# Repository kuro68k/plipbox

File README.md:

# plipbox

PCB for lallafa's plipbox (http://lallafa.de/blog/amiga-projects/plipbox/).

Allows an Amiga to connect to an ethernet network via the parallel port. Very low cost, uses an Arduino Nano V3 and ethernet shield.

This PCB is 2 layers. There is no cost advantage to single layer when ordering from Chinese manufacturers like Seeed Studio, and two layers means no need for jumper wires.

In addition there is a low cost TTL to RS232 level shifter. It's entirely optional, and if fitted allows the Amiga to configure the plipbox via connection to the serial port.

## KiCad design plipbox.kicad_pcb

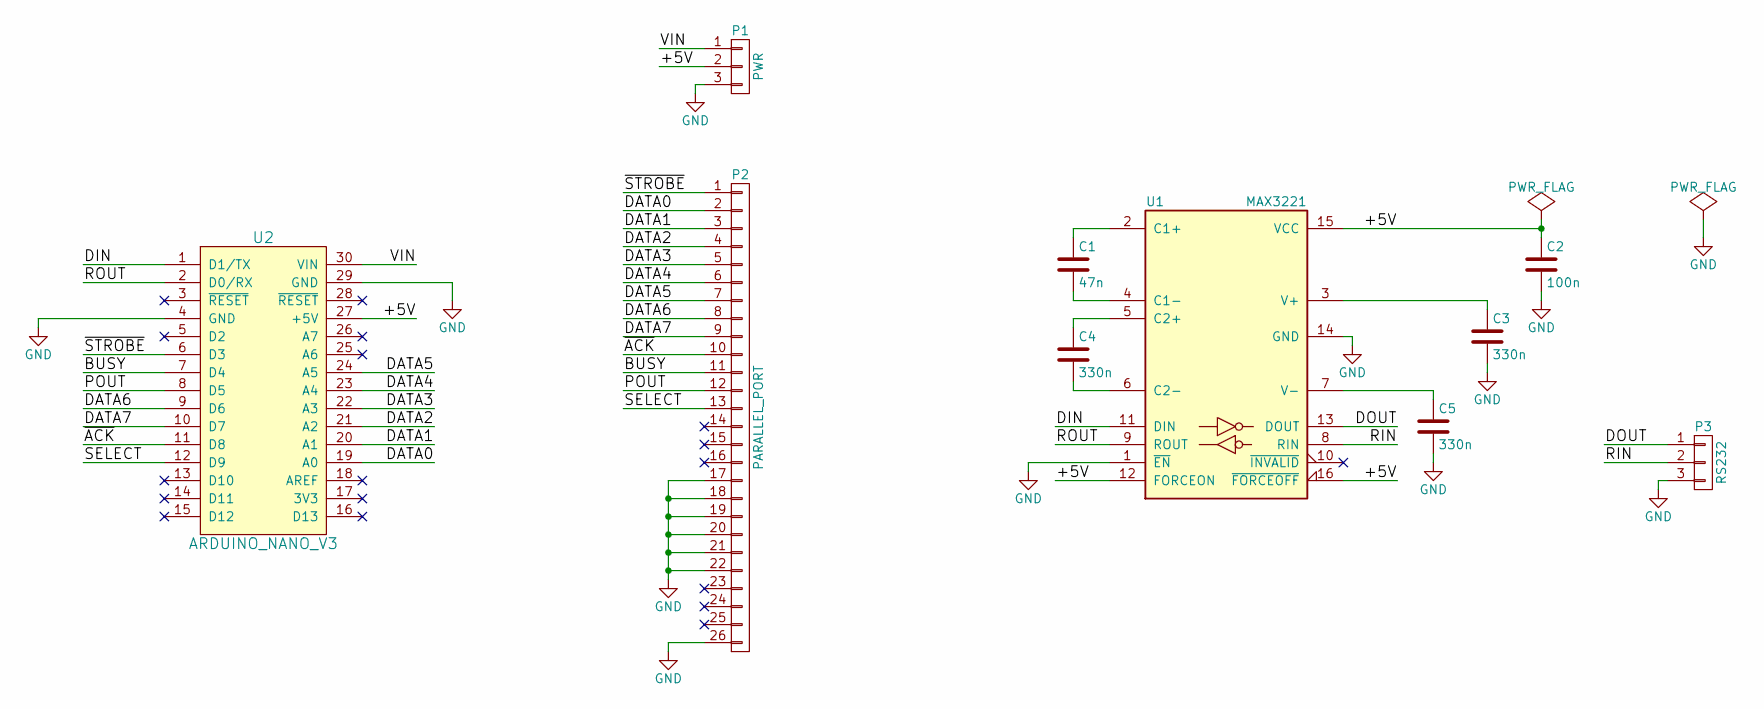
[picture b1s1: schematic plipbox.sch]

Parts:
C1: 47n; C_0603_HandSoldering
C2: 100n; C_0603_HandSoldering
C3, C4, C5: 330n; C_0603_HandSoldering
P1: PWR; Pin_Header_Straight_1x03_Pitch2.54mm
P2: PARALLEL_PORT; DB25M-RA-TH
P3: RS232; Pin_Header_Straight_1x03_Pitch2.54mm
U1: MAX3221; TSSOP-16_4.4x5mm_Pitch0.65mm
U2: ARDUINO_NANO_V3; DIP-30_W15.24mm_LongPads

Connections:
/+5V: C2.1, P1.2, U1.12 (FORCEON), U1.15 (VCC), U1.16 (~FORCEOFF), U2.27 (+5V)
/BUSY: P2.11, U2.7 (D4)
/DATA0: P2.2, U2.19 (A0)
/DATA1: P2.3, U2.20 (A1)
/DATA2: P2.4, U2.21 (A2)
/DATA3: P2.5, U2.22 (A3)
/DATA4: P2.6, U2.23 (A4)
/DATA5: P2.7, U2.24 (A5)
/DATA6: P2.8, U2.9 (D6)
/DATA7: P2.9, U2.10 (D7)
/DIN: U1.11 (DIN), U2.1 (D1/TX)
/DOUT: P3.1, U1.13 (DOUT)
/POUT: P2.12, U2.8 (D5)
/RIN: P3.2, U1.8 (RIN)
/ROUT: U1.9 (ROUT), U2.2 (D0/RX)
/SELECT: P2.13, U2.12 (D9)
/VIN: P1.1, U2.30 (VIN)
/~ACK: P2.10, U2.11 (D8)
/~STROBE: P2.1, U2.6 (D3)
GND: C2.2, C3.2, C5.2, P1.3, P2.17, P2.18, P2.19, P2.20, P2.21, P2.22, P2.26, P3.3, U1.1 (~EN), U1.14 (GND), U2.4 (GND), U2.29 (GND)
unnamed: C1.1, U1.2 (C1+)
unnamed: C1.2, U1.4 (C1-)
unnamed: C3.1, U1.3 (V+)
unnamed: C4.1, U1.5 (C2+)
unnamed: C4.2, U1.6 (C2-)
unnamed: C5.1, U1.7 (V-)

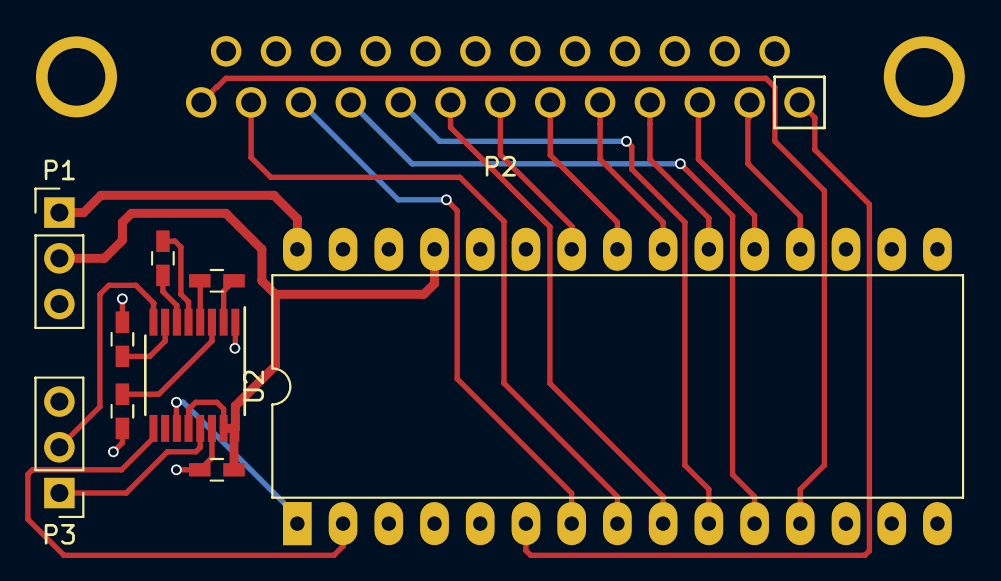
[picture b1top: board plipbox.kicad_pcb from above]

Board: 2 copper layers, 10 parts (0 on the bottom side), 26 nets.

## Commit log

2017-07-02 :tada: Added .gitattributes & .gitignore files
2017-07-02 ERC power flag errors
2017-07-02 Started PCB
2017-07-03 Routing
2017-07-03 Board outline
2017-07-03 More compact U1
2017-07-03 Routed, DRC OK
2017-07-09 Silkscreen
2017-07-09 Fixed DB25M footprint
2017-07-09 Plot
2017-07-09 Imperial drill file for Seeed
2017-07-25 Created
2020-12-31 Create LICENSE
